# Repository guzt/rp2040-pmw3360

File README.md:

A WIP split keyboard with a USB hub and two trackballs in the center:

1. an optical trackball for mouse control
1. a tiny blackberry trackball for scroll

Based on:

# RP2040+PMW3360

This repository contains design files and code for a PCB carrying Raspberry Pi's RP2040 chip and the PixArt PMW3360 optical mouse sensor. They can be used for rapid prototyping of USB mice and trackballs.

The files in the [fabrication](fabrication) folder can be used to order this board from JLCPCB with SMT assembly. The board you get includes everything except the sensor. If some of the specific components are out of stock, try to find an equivalent with the same package and parameters.

The sensor chip should be soldered on the bottom side (the opposite side from all the other components). The dot marks pin 1. The optic goes on the top side.

If you're looking for a convenient way of mounting mouse button switches in a case, perhaps [this repository](https://github.com/jfedor2/mouse-switch-mount-pcb) will be of use.

Examples of devices made using this board:

* [Trackball 7](https://www.prusaprinters.org/prints/83631-trackball-7)
* [Trackball 8](https://www.prusaprinters.org/prints/84148-trackball-8)
* [Spherical trackball](https://www.prusaprinters.org/prints/85053-spherical-trackball)
* [Two-ball trackball](https://github.com/jfedor2/two-ball-trackball)
* [Mouse 1](https://www.prusaprinters.org/prints/87379-mouse-1)
* [Mouse 2](https://www.prusaprinters.org/prints/88403-mouse-2)
* [Trackball with twist-to-scroll](https://github.com/jfedor2/twist-to-scroll-trackball)
* [Trackball with scroll ring](https://github.com/jfedor2/scroll-ring-trackball)
* [Mouse 4](https://www.prusaprinters.org/prints/127451-mouse-4)
* [Trackball 15](https://www.prusaprinters.org/prints/131450-trackball-15), [15b/c](https://www.printables.com/model/263616-trackball-15bc), [15d/e](https://www.printables.com/model/267954-trackball-15de)

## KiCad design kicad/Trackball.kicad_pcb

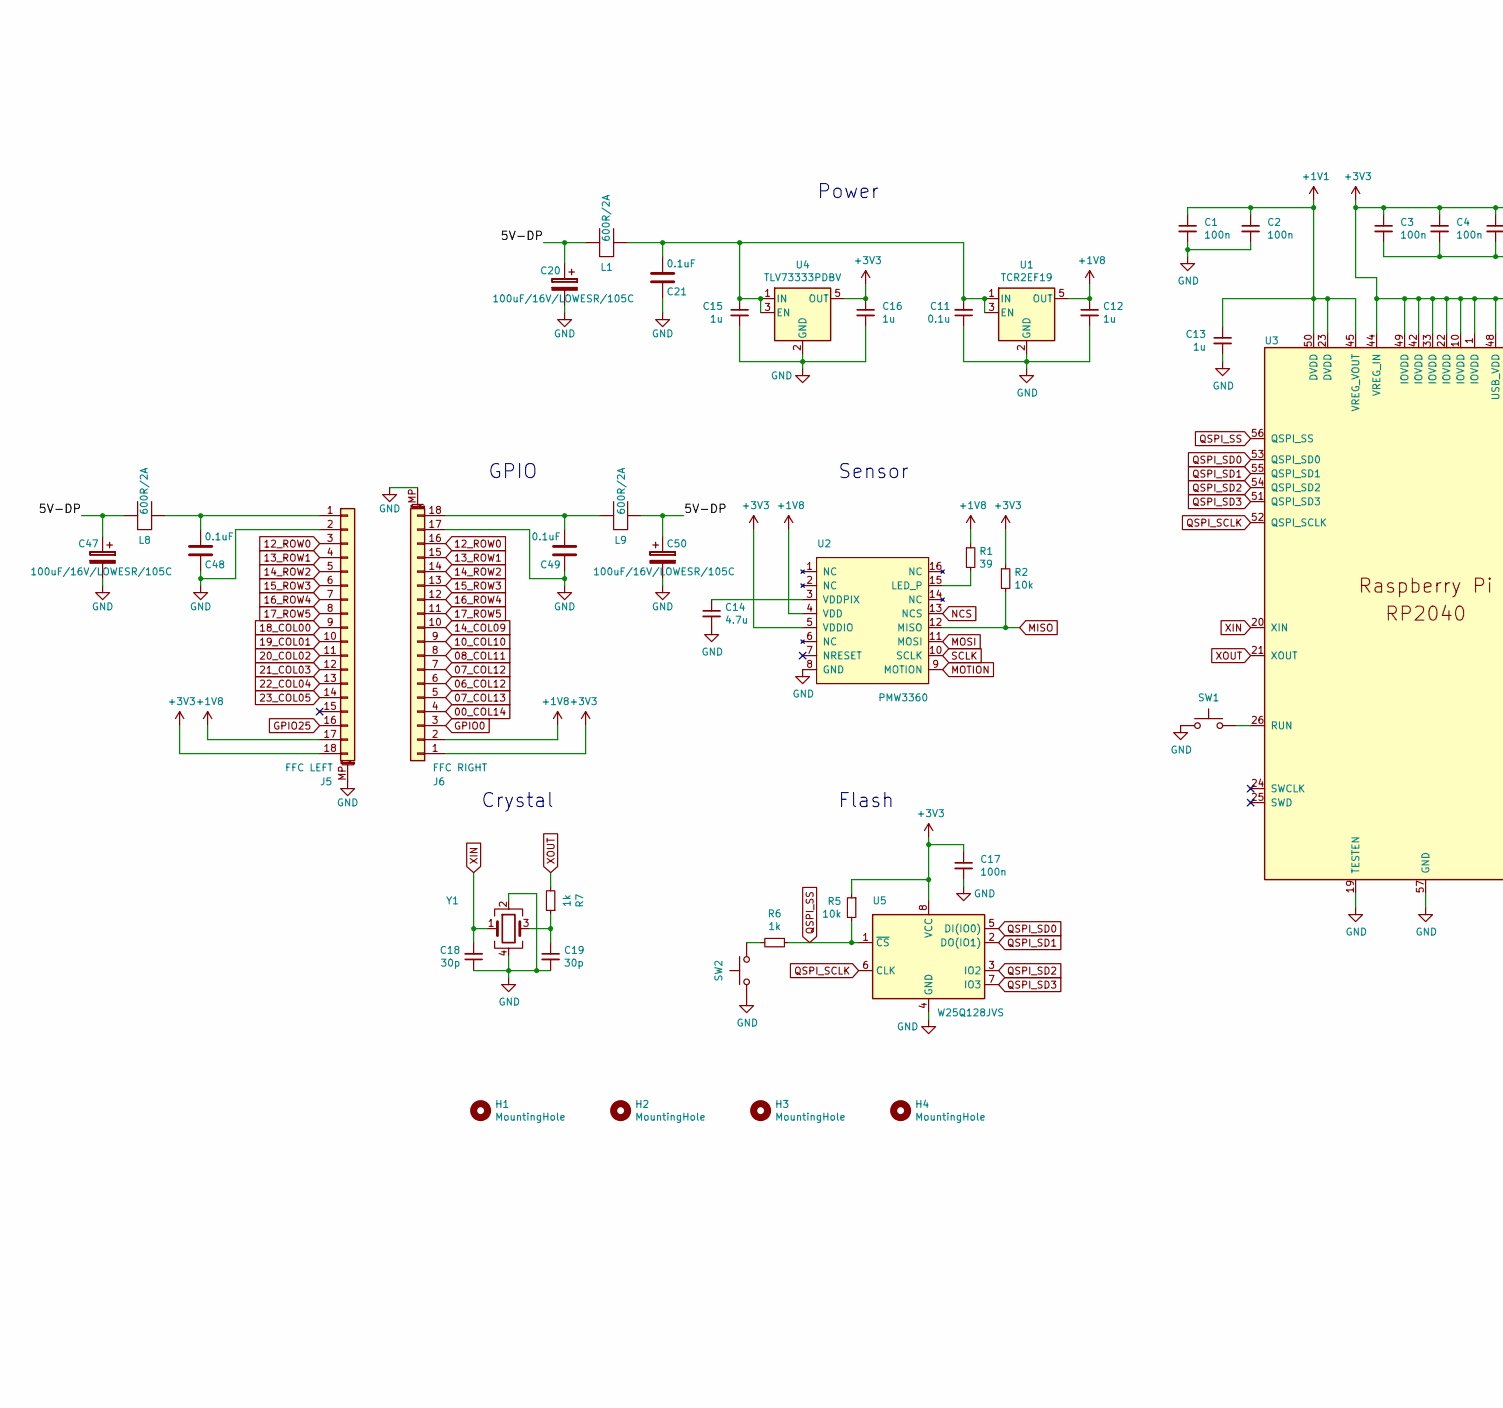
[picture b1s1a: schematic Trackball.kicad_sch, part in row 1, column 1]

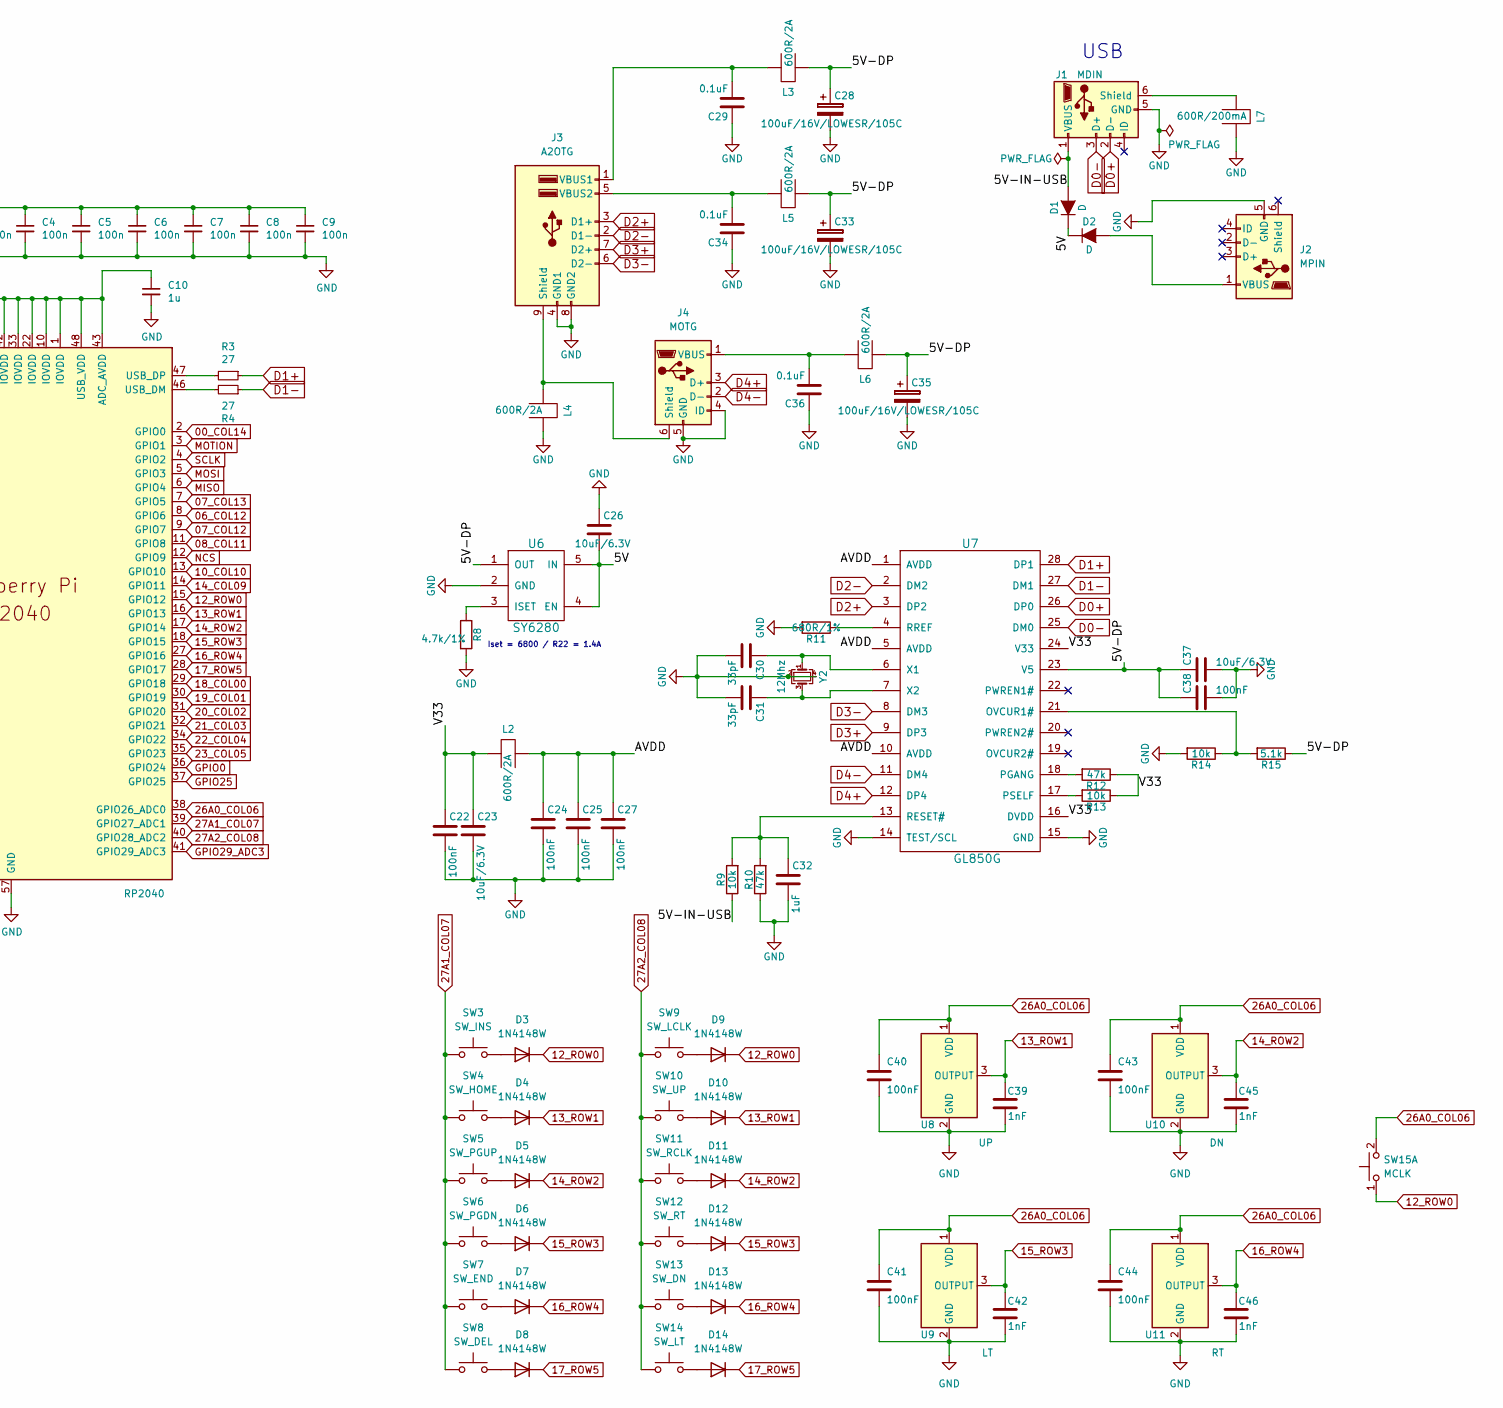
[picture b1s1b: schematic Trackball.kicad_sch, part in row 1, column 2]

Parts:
C1, C2, C3, C4, C5, C6, C7, C8, C9, C17: 100n; C_0402_1005Metric; LCSC C1525
C10, C13, C15, C16: 1u; C_0402_1005Metric; LCSC C52923
C11: 0.1u; C_0402_1005Metric; LCSC C14663
C12: 1u; C_0402_1005Metric; LCSC C15849
C14: 4.7u; C_0402_1005Metric; LCSC C23733
C18, C19: 30p; C_0402_1005Metric; LCSC C1570
C20, C28, C33, C35, C47, C50: 100uF/16V/LOWESR/105C; CP_Elec_6.3x5.9
C21, C29, C34, C36, C48, C49: 0.1uF; C_0402_1005Metric
C22, C24, C25, C27, C38, C40, C41, C43, C44: 100nF; C_0402_1005Metric
C23, C26, C37: 10uF/6.3V; C_0402_1005Metric
C30, C31: 33pF; C_0402_1005Metric
C32: 1uF; C_0402_1005Metric
C39, C42, C45, C46: 1nF; C_0402_1005Metric
D1, D2: D; D_SOD-323
D3, D4, D5, D6, D7, D8, D9, D10, D11, D12, D13, D14: 1N4148W; D_SOD-323
H1, H2, H3, H4: MountingHole; MountingHole_3.2mm_M3
J1: MDIN; USB_Micro-B_Molex-105017-0001
J2: MPIN; USB_Micro-B_Molex-105017-0001
J3: A2OTG; USB_A_Wuerth_61400826021_Horizontal_Stacked
J4: MOTG; USB_Micro-B_Molex-105017-0001
J5: FFC LEFT; TE_1-1734839-8_1x18-1MP_P0.5mm_Horizontal
J6: FFC RIGHT; TE_1-1734839-8_1x18-1MP_P0.5mm_Horizontal
L1, L2, L3, L4, L5, L6, L8, L9: 600R/2A; R_0805_2012Metric
L7: 600R/200mA; R_0805_2012Metric
R1: 39; R_0402_1005Metric; LCSC C25110
R2, R5: 10k; R_0402_1005Metric; LCSC C25744
R3, R4: 27; R_0402_1005Metric; LCSC C138021
R6, R7: 1k; R_0402_1005Metric; LCSC C11702
R8: 4.7k/1%; R_0402_1005Metric
R9, R13, R14: 10k; R_0402_1005Metric
R10, R12: 47k; R_0402_1005Metric
R11: 680R/1%; R_0402_1005Metric
R15: 5.1k; R_0402_1005Metric
SW1: RUN; SW_SPST_Omron_B3FS-100xP; LCSC C271750
SW2: FLASH; SW_SPST_Omron_B3FS-100xP; LCSC C271750
SW3: SW_INS; SW_Cherry_MX_1.00u_PCB
SW4: SW_HOME; SW_Cherry_MX_1.00u_PCB
SW5: SW_PGUP; SW_Cherry_MX_1.00u_PCB
SW6: SW_PGDN; SW_Cherry_MX_1.00u_PCB
SW7: SW_END; SW_Cherry_MX_1.00u_PCB
SW8: SW_DEL; SW_Cherry_MX_1.00u_PCB
SW9: SW_LCLK; SW_Cherry_MX_2.00u_Vertical_PCB
SW10: SW_UP; SW_Cherry_MX_1.00u_PCB
SW11: SW_RCLK; SW_Cherry_MX_2.00u_Vertical_PCB
SW12: SW_RT; SW_Cherry_MX_1.00u_PCB
SW13: SW_DN; SW_Cherry_MX_1.00u_PCB
SW14: SW_LT; SW_Cherry_MX_1.00u_PCB
SW15: MCLK; SW_SPST_TL3342
U1: TCR2EF19; SOT-23-5; LCSC C146366
U2: PMW3360
U3: RP2040; RP2040-QFN-56; LCSC C2040
U4: TLV73333PDBV; SOT-23-5; LCSC C134139
U5: W25Q128JVS; SOIC-8_5.23x5.23mm_P1.27mm; LCSC C97521
U6: SY6280; SOT-23-5
U7: GL850G; SSOP-28_5.3x10.2mm_P0.65mm
U8: UP; MT8691DT-1608
U9: LT; MT8691DT-1608
U10: DN; MT8691DT-1608
U11: RT; MT8691DT-1608
Y1: 12MHz; Crystal_SMD_3225-4Pin_3.2x2.5mm; LCSC C9002
Y2: 12Mhz; Crystal_SMD_3225-4Pin_3.2x2.5mm

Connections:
00_COL14: J6.4, U3.2 (GPIO0)
06_COL12: J6.6, U3.8 (GPIO6)
07_COL12: J6.7, U3.9 (GPIO7)
07_COL13: J6.5, U3.7 (GPIO5)
08_COL11: J6.8, U3.11 (GPIO8)
10_COL10: J6.9, U3.13 (GPIO10)
12_ROW0: D3.1 (K), D9.1 (K), J5.3, J6.16, SW15.1 (C), U3.15 (GPIO12)
13_ROW1: C39.1, D4.1 (K), D10.1 (K), J5.4, J6.15, U3.16 (GPIO13), U8.3 (OUTPUT)
14_COL09: J6.10, U3.14 (GPIO11)
14_ROW2: C45.1, D5.1 (K), D11.1 (K), J5.5, J6.14, U3.17 (GPIO14), U10.3 (OUTPUT)
15_ROW3: C42.1, D6.1 (K), D12.1 (K), J5.6, J6.13, U3.18 (GPIO15), U9.3 (OUTPUT)
16_ROW4: C46.1, D7.1 (K), D13.1 (K), J5.7, J6.12, U3.27 (GPIO16), U11.3 (OUTPUT)
17_ROW5: D8.1 (K), D14.1 (K), J5.8, J6.11, U3.28 (GPIO17)
18_COL00: J5.9, U3.29 (GPIO18)
19_COL01: J5.10, U3.30 (GPIO19)
20_COL02: J5.11, U3.31 (GPIO20)
21_COL03: J5.12, U3.32 (GPIO21)
22_COL04: J5.13, U3.34 (GPIO22)
23_COL05: J5.14, U3.35 (GPIO23)
26A0_COL06: C40.2, C41.2, C43.2, C44.2, SW15.2 (D), U3.38 (GPIO26_ADC0), U8.1 (VDD), U9.1 (VDD), U10.1 (VDD), U11.1 (VDD)
27A1_COL07: SW3.1, SW4.1, SW5.1, SW6.1, SW7.1, SW8.1, U3.39 (GPIO27_ADC1)
27A2_COL08: SW9.1, SW10.1, SW11.1, SW12.1, SW13.1, SW14.1, U3.40 (GPIO28_ADC2)
+1V1: C1.1, C2.1, C13.1, U3.23 (DVDD), U3.45 (VREG_VOUT), U3.50 (DVDD)
+1V8: C12.1, J5.17, J6.2, R1.1, U1.5 (OUT), U2.4 (VDD)
+3V3: C3.1, C4.1, C5.1, C6.1, C7.1, C8.1, C9.1, C10.1, C16.1, C17.1, J5.18, J6.1, R2.1, R5.1, U2.5 (VDDIO), U3.1 (IOVDD), U3.10 (IOVDD), U3.22 (IOVDD), U3.33 (IOVDD), U3.42 (IOVDD), U3.43 (ADC_AVDD), U3.44 (VREG_IN), U3.48 (USB_VDD), U3.49 (IOVDD), U4.5 (OUT), U5.8 (VCC)
/5V: C26.2, D1.1 (K), D2.1 (K), U6.4 (EN), U6.5 (IN)
/5V-DP: C20.1, C28.1, C33.1, C35.1, C37.1, C38.1, C47.1, C50.1, L1.1, L3.1, L5.1, L6.1, L8.1, L9.1, R15.1, U6.1 (OUT), U7.23 (V5)
/5V-IN-USB: D1.2 (A), J1.1 (VBUS), R9.1
/AVDD: C24.1, C25.1, C27.1, L2.2, U7.1 (AVDD), U7.5 (AVDD), U7.10 (AVDD)
/V33: C22.1, C23.1, L2.1, R12.1, R13.1, U7.16 (DVDD), U7.24 (V33)
D0+: J1.2 (D-), U7.26 (DP0)
D0-: J1.3 (D+), U7.25 (DM0)
D1+: R3.1, U7.28 (DP1)
D1-: R4.1, U7.27 (DM1)
D2+: J3.3 (D1+), U7.3 (DP2)
D2-: J3.2 (D1-), U7.2 (DM2)
D3+: J3.7 (D2+), U7.9 (DP3)
D3-: J3.6 (D2-), U7.8 (DM3)
D4+: J4.3 (D+), U7.12 (DP4)
D4-: J4.2 (D-), U7.11 (DM4)
GND: C1.2, C2.2, C3.2, C4.2, C5.2, C6.2, C7.2, C8.2, C9.2, C10.2, C11.1, C12.2, C13.2, C14.2, C15.2, C16.2, C17.2, C18.1, C19.2, C20.2, C21.1, C22.2, C23.2, C24.2, C25.2, C26.1, C27.2, C28.2, C29.1, C30.2, C31.2, C32.2, C33.2, C34.1, C35.2, C36.1, C37.2, C38.2, C39.2, C40.1, C41.1, C42.2, C43.1, C44.1, C45.2, C46.2, C47.2, C48.1, C49.1, C50.2, J1.5 (GND), J2.5 (GND), J3.4 (GND1), J3.8 (GND2), J4.4 (ID), J4.5 (GND), J5.2, J5.MP (MountPin), J6.17, J6.MP (MountPin), L4.2, L7.2, R8.2, R10.1, R11.2, R14.2, SW1.1, SW2.1, U1.2 (GND), U2.8 (GND), U3.19 (TESTEN), U3.57 (GND), U4.2 (GND), U5.4 (GND), U6.2 (GND), U7.14 (TEST/SCL), U7.15 (GND), U8.2 (GND), U9.2 (GND), U10.2 (GND), U11.2 (GND), Y1.2, Y1.4, Y2.2, Y2.4
GPIO0: J6.3, U3.36 (GPIO24)
GPIO25: J5.16, U3.37 (GPIO25)
GPIO29_ADC3: U3.41 (GPIO29_ADC3)
MISO: R2.2, U2.12 (MISO), U3.6 (GPIO4)
MOSI: U2.11 (MOSI), U3.5 (GPIO3)
MOTION: U2.9 (MOTION), U3.3 (GPIO1)
NCS: U2.13 (NCS), U3.12 (GPIO9)
unnamed: C11.2, C15.1, C21.2, L1.2, U1.1 (IN), U1.3 (EN), U4.1 (IN), U4.3 (EN)
unnamed: C14.1, U2.3 (VDDPIX)
unnamed: C19.1, R7.1, Y1.3
unnamed: C29.2, J3.1 (VBUS1), L3.2
unnamed: C30.1, U7.6 (X1), Y2.1
unnamed: C31.1, U7.7 (X2), Y2.3
unnamed: C32.1, R9.2, R10.2, U7.13 (RESET#)
unnamed: C34.2, J3.5 (VBUS2), L5.2
unnamed: C36.2, J4.1 (VBUS), L6.2
unnamed: C48.2, J5.1, L8.2
unnamed: C49.2, J6.18, L9.2
unnamed: D2.2 (A), J2.1 (VBUS)
unnamed: D3.2 (A), SW3.2
unnamed: D4.2 (A), SW4.2
unnamed: D5.2 (A), SW5.2
unnamed: D6.2 (A), SW6.2
unnamed: D7.2 (A), SW7.2
unnamed: D8.2 (A), SW8.2
unnamed: D9.2 (A), SW9.2
unnamed: D10.2 (A), SW10.2
unnamed: D11.2 (A), SW11.2
unnamed: D12.2 (A), SW12.2
unnamed: D13.2 (A), SW13.2
unnamed: D14.2 (A), SW14.2
unnamed: J1.6 (Shield), L7.1
unnamed: J3.9 (Shield), J4.6 (Shield), L4.1
unnamed: R1.2, U2.15 (LED_P)
unnamed: R3.2, U3.47 (USB_DP)
unnamed: R4.2, U3.46 (USB_DM)
unnamed: R6.2, SW2.2
unnamed: R8.1, U6.3 (ISET)
unnamed: R11.1, U7.4 (RREF)
unnamed: R12.2, U7.18 (PGANG)
unnamed: R13.2, U7.17 (PSELF)
unnamed: R14.1, R15.2, U7.21 (OVCUR1#)
unnamed: SW1.2, U3.26 (RUN)
QSPI_SCLK: U3.52 (QSPI_SCLK), U5.6 (CLK)
QSPI_SD0: U3.53 (QSPI_SD0), U5.5 (DI(IO0))
QSPI_SD1: U3.55 (QSPI_SD1), U5.2 (DO(IO1))
QSPI_SD2: U3.54 (QSPI_SD2), U5.3 (IO2)
QSPI_SD3: U3.51 (QSPI_SD3), U5.7 (IO3)
QSPI_SS: R5.2, R6.1, U3.56 (QSPI_SS), U5.1 (~CS)
SCLK: U2.10 (SCLK), U3.4 (GPIO2)
XIN: C18.2, U3.20 (XIN), Y1.1
XOUT: R7.2, U3.21 (XOUT)

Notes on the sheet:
GPIO
Crystal
Sensor
Power
Iset = 6800 / R22 = 1.4A
USB
Flash

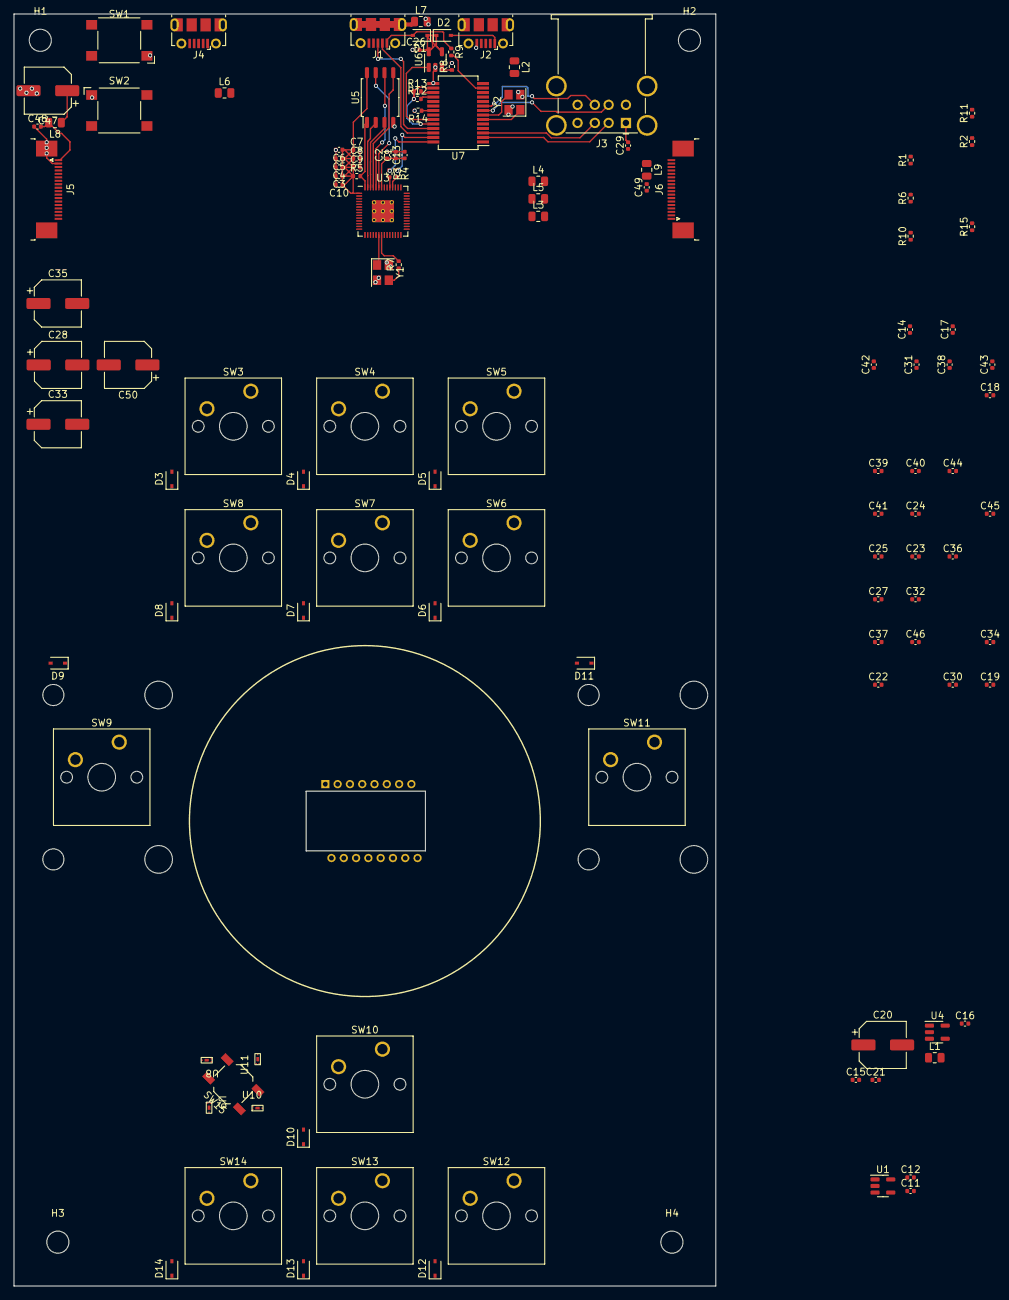
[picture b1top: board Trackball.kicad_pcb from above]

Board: 2 copper layers, 101.6 x 184.2 mm, 126 parts (1 on the bottom side), 92 nets.

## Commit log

2022-10-04 add initial keyboard schematics and pcb
2022-10-05 progress
